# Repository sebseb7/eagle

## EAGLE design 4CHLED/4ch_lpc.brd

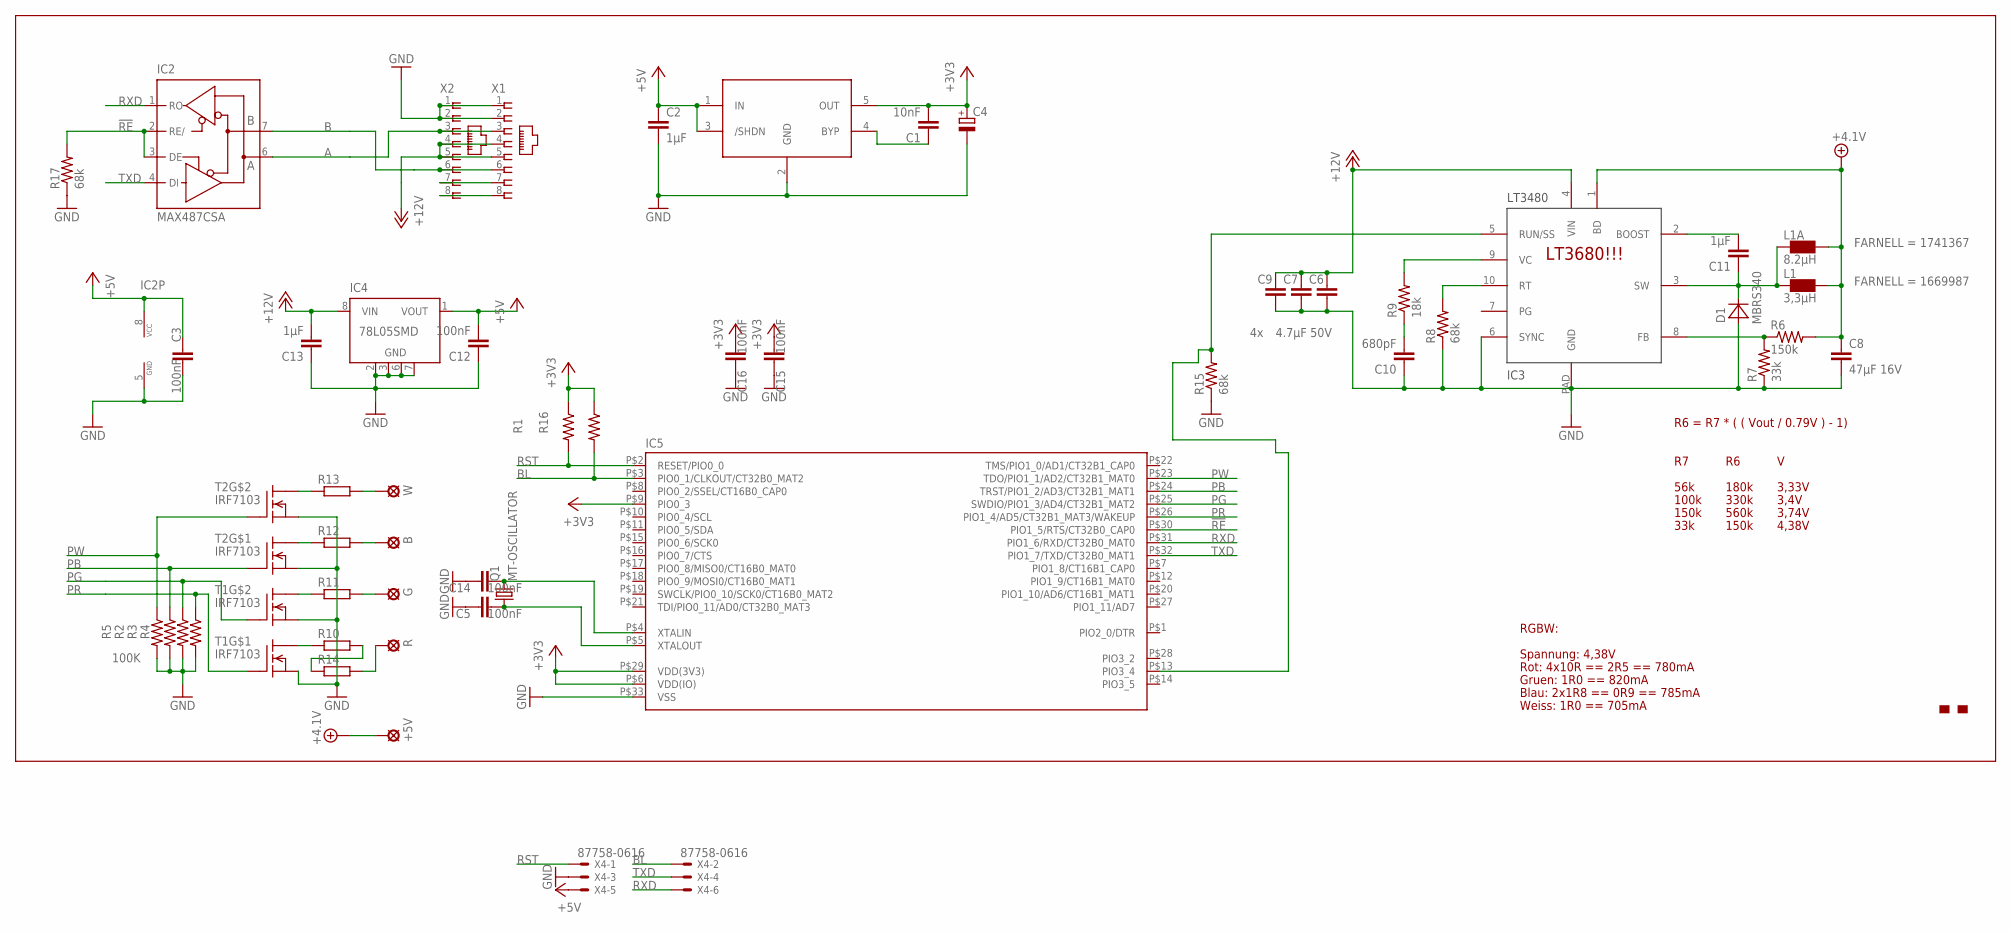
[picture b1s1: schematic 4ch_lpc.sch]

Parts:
+5V: SE14
B: SE14
C1: 10nF; C0402
C2, C11, C13: 1µF; 0805
C3, C5, C12, C14, C15, C16: 100nF; 0402-CAP
C4: CPOL-EUSMCA; SMC_A
C6, C7, C9: 4.7µF 50V; 1210
C8: 47µF 16V; 1210
C10: 680pF; 0805
D1: MBRS340; DO214AB
G: SE14
IC1: LT1761; SOT23-5L
IC2: MAX487CSA; SO08
IC3: LT3972; MSOP10-PAD
IC4: 78L05SMD; SO08
IC5: LPC1113/4_QFN; HVQFN33-7X7
L1: 3,3µH; RLF7030; FARNELL 1669987
L1A: 8.2µH; IHLP-2525CZ; FARNELL 1741367
Q1: MT-OSCILLATOR; MT
R: SE14
R1, R2, R3, R4, R5, R16: 100K; 0402-RES
R6: 150k; 0805
R7: 33k; 0805
R8: 68k; 0805
R9: 18k; 0805
R10, R11, R12, R13, R14: R-EU_MELF0207R; MINI_MELF-0207R
R15, R17: 68k; 0402-RES
T1, T2: IRF7103; SO-8
U$1: MAKE-DD_LOGO'PROMPT'; MAKE-DD_LOGO_PROMPT
W: SE14
X1, X2: RJ45-8L-B; RJ45-NO-SHIELD
X4: 87758-0616

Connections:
!RE: IC2.2 (RE/), IC2.3 (DE), IC5.P$30 (PIO1_5/RTS/CT32B0_CAP0), R17.2
+3V3: C1.2, C4.+, C15.2, C16.2, IC1.5 (OUT), IC5.P$6 (VDD(IO)), IC5.P$9 (PIO0_3), IC5.P$29 (VDD(3V3)), R1.1, R16.1
+4.1V: +5V.MP, C8.1, IC3.1 (BD), L1.P$1 (1), L1A.P$1 (1), R6.2
+5V: C2.1, C3.1, C12.2, IC1.1 (IN), IC1.3 (/SHDN), IC2.8 (VCC), IC4.1 (VOUT), X4.5
+12V: C6.1, C7.1, C9.1, C13.2, IC3.4 (VIN), IC4.8 (VIN), X1.4, X1.5, X2.4, X2.5
A: IC2.6 (A), X1.3, X2.3
B: IC2.7 (B), X1.6, X2.6
BL: IC5.P$3 (PIO0_1/CLKOUT/CT32B0_MAT2), R16.2, X4.2
GND: C2.2, C3.2, C4.-, C5.1, C6.2, C7.2, C8.2, C9.2, C10.1, C12.1, C13.1, C14.1, C15.1, C16.1, D1.A, IC1.2 (GND), IC2.5 (GND), IC3.6 (SYNC), IC3.PAD (GND), IC4.2 (GND), IC4.3 (GND), IC4.6 (GND), IC4.7 (GND), IC5.P$33 (VSS), R2.2, R3.2, R4.2, R5.2, R7.1, R8.1, R15.1, R17.1, T1.1 (S), T1.3 (S), T2.1 (S), T2.3 (S), X1.1, X1.2, X2.1, X2.2, X4.3
unnamed: R10.1, T1.8 (D1)
unnamed: R13.2, W.MP
unnamed: R13.1, T2.5 (D1)
unnamed: R11.1, T1.5 (D1)
unnamed: R12.1, T2.8 (D1)
unnamed: IC3.10 (RT), R8.2
unnamed: C1.1, IC1.4 (BYP)
unnamed: G.MP, R11.2
unnamed: B.MP, R12.2
unnamed: C10.2, R9.1
unnamed: R10.2, R14.1
unnamed: IC3.5 (RUN/SS), IC5.P$13 (PIO3_4), R15.2
unnamed: R.MP, R14.2
unnamed: IC3.9 (VC), R9.2
unnamed: C11.1, D1.K (C), IC3.3 (SW), L1.P$2 (2), L1A.P$2 (2)
unnamed: IC3.8 (FB), R6.1, R7.2
unnamed: C11.2, IC3.2 (BOOST)
unnamed: X1.7, X2.7
unnamed: X1.8, X2.8
unnamed: C5.2, IC5.P$5 (XTALOUT), Q1.1
unnamed: C14.2, IC5.P$4 (XTALIN), Q1.3 (2)
PB: IC5.P$24 (TRST/PIO1_2/AD3/CT32B1_MAT1), R2.1, T2.2 (G)
PG: IC5.P$25 (SWDIO/PIO1_3/AD4/CT32B1_MAT2), R3.1, T1.4 (G)
PR: IC5.P$26 (PIO1_4/AD5/CT32B1_MAT3/WAKEUP), R4.1, T1.2 (G)
PW: IC5.P$23 (TDO/PIO1_1/AD2/CT32B1_MAT0), R5.1, T2.4 (G)
RST: IC5.P$2 (RESET/PIO0_0), R1.2, X4.1
RXD: IC2.1 (RO), IC5.P$31 (PIO1_6/RXD/CT32B0_MAT0), X4.6
TXD: IC2.4 (DI), IC5.P$32 (PIO1_7/TXD/CT32B0_MAT1), X4.4

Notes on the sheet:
R6 = R7 * ( ( Vout / 0.79V ) - 1)
56k
180k
3,33V
100k
330k
3,4V
150k
560k
3,74V
33k
4,38V
RGBW:
Spannung: 4,38V
Rot: 4x10R == 2R5 == 780mA
Gruen: 1R0 == 820mA
Blau: 2x1R8 == 0R9 == 785mA
Weiss: 1R0 == 705mA
LT3680!!!

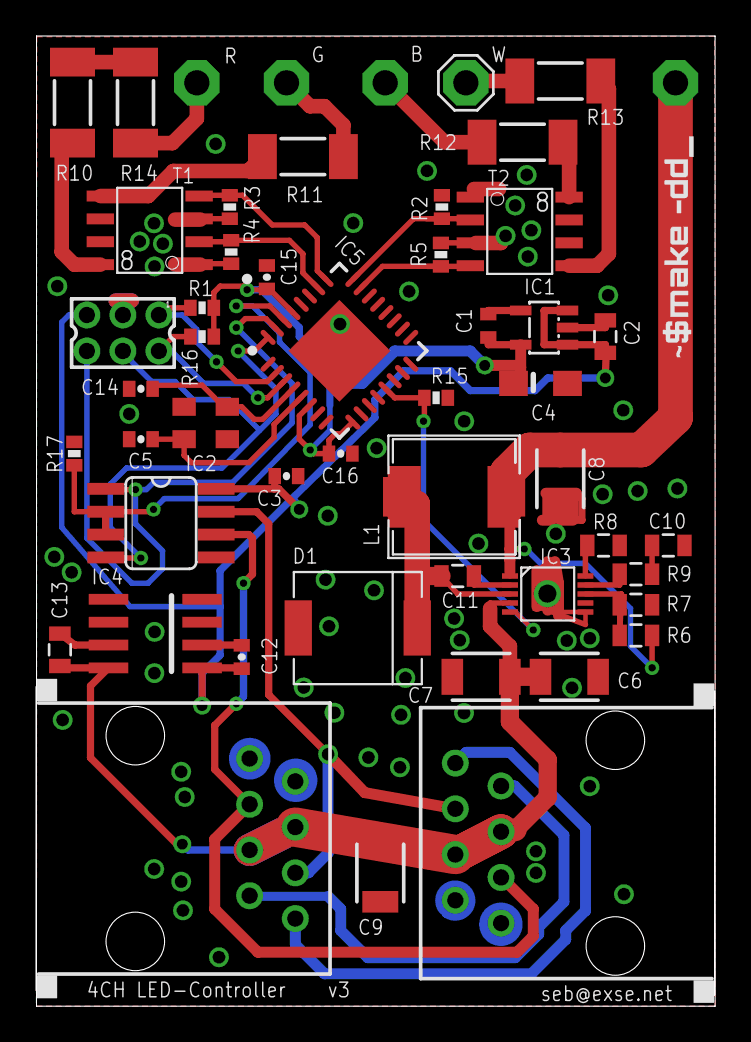
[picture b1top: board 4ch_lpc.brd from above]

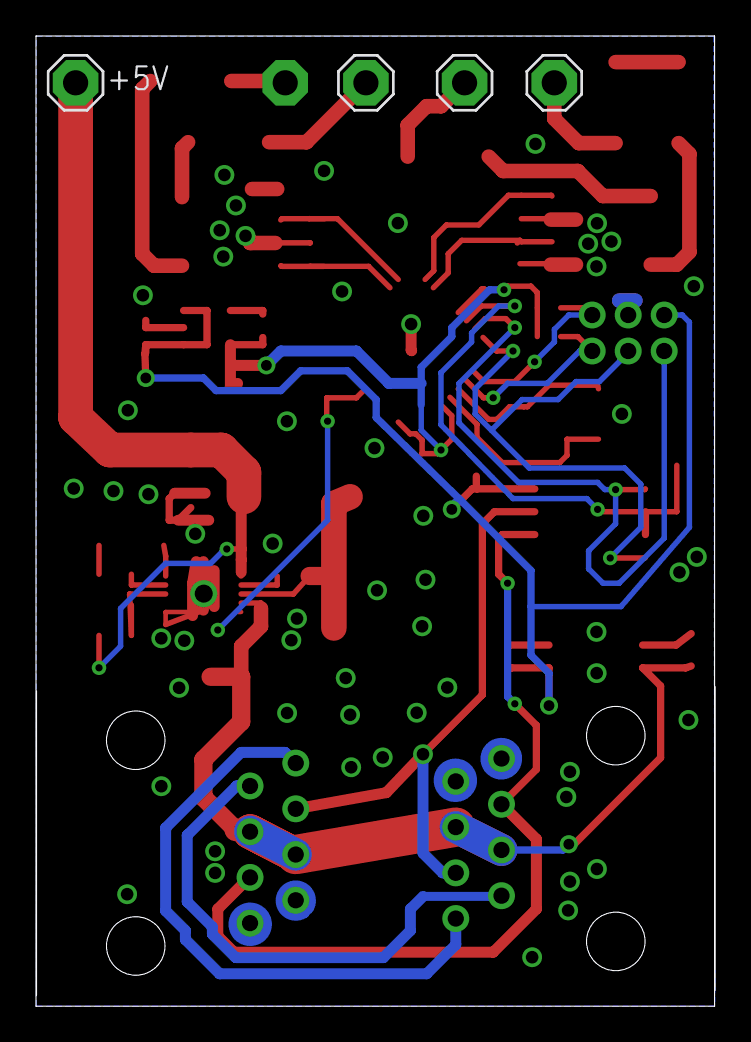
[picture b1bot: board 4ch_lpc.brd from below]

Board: 2 copper layers, 37.7 x 53.9 mm, 53 parts (4 on the bottom side), 37 nets.

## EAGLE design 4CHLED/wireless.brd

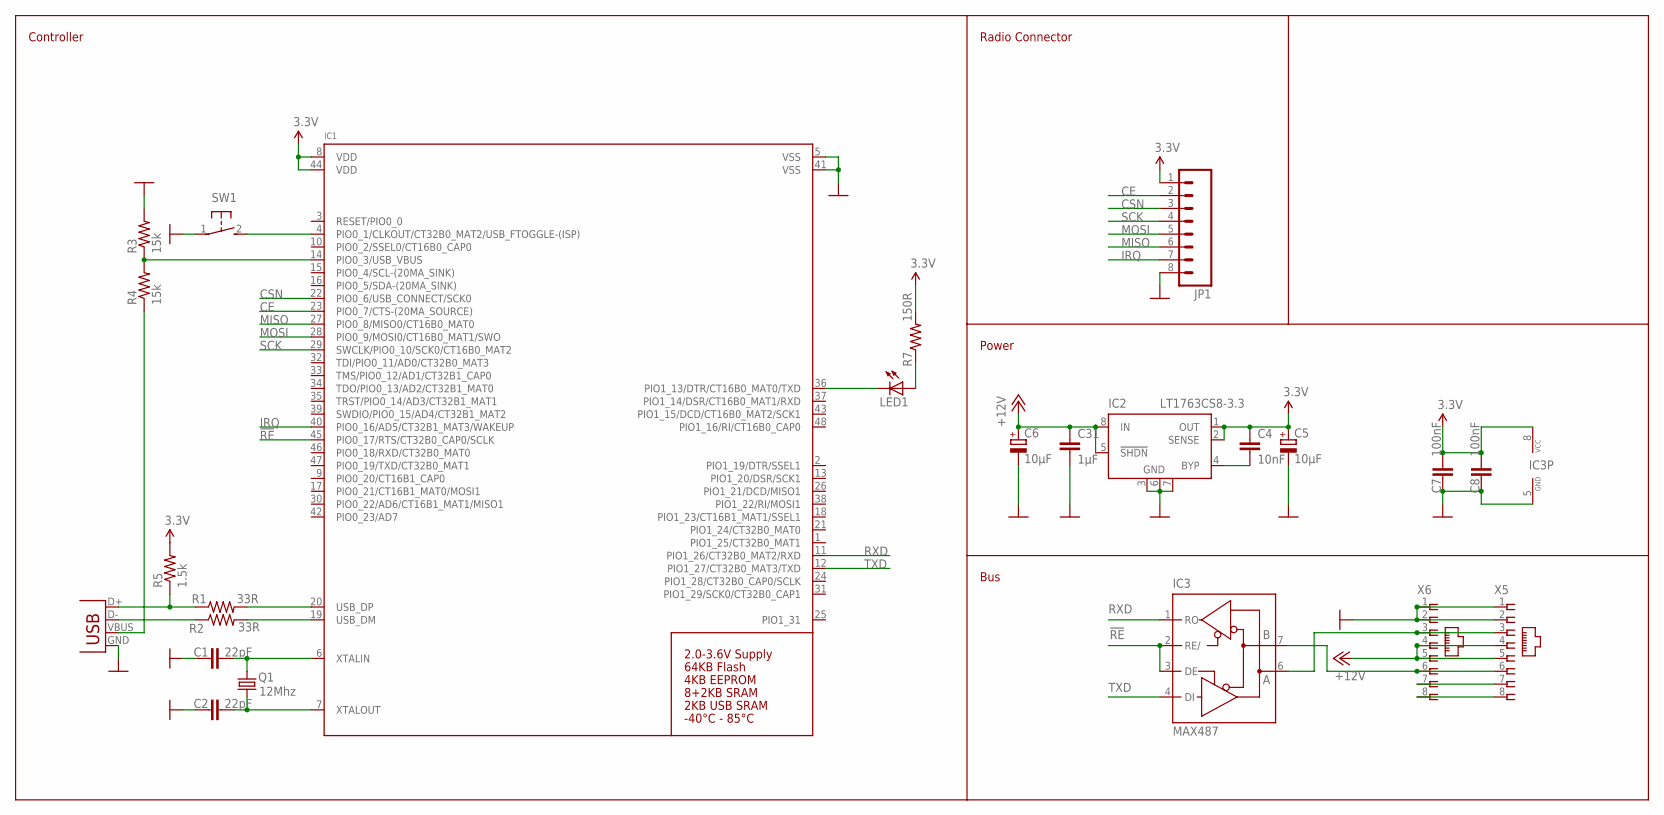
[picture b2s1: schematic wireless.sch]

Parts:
C1, C2: 22pF; 0402-CAP
C4: 10nF; 0402-CAP
C5: 10µF; SMC_A
C6: 10µF; SMC_D
C7, C8: 100nF; 0402-CAP
C31: 1µF; 0805
IC1: LPC1347_QFP48; LQFP48
IC2: LT1763CS8-3.3; SOIC8
IC3: MAX487; SO08
JP1: M081X08; 1X08
LED1: LEDCHIPLED_0805; CHIPLED_0805
Q1: 12Mhz; X22
R1, R2: 33R; 0402-RES
R3, R4: 15k; 0402-RES
R5: 1.5k; 0402-RES
R7: 150R; 0402-RES
SW1: SWITCH_MCTAEF
X1: USBSMD; USB-MINIB
X5, X6: RJ45-8L-B; RJ45-NO-SHIELD

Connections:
3.3V: C4.1, C5.+, C7.2, C8.2, IC1.8 (VDD), IC1.44 (VDD), IC2.1 (OUT), IC2.2 (SENSE), IC3.8 (VCC), JP1.1, R5.2, R7.2
!RE: IC1.45 (PIO0_17/RTS/CT32B0_CAP0/SCLK), IC3.2 (RE/), IC3.3 (DE)
+12V: C6.+, C31.1, IC2.5 (!SHDN), IC2.8 (IN), X5.4, X5.5, X6.4, X6.5
A1: IC3.6 (A), X5.3, X6.3
B1: IC3.7 (B), X5.6, X6.6
CE: IC1.23 (PIO0_7/CTS-(20MA_SOURCE)), JP1.2
CSN: IC1.22 (PIO0_6/USB_CONNECT/SCK0), JP1.3
GND: C1.1, C2.1, C5.-, C6.-, C7.1, C8.1, C31.2, IC1.5 (VSS), IC1.41 (VSS), IC2.3 (GND), IC2.6 (GND), IC2.7 (GND), IC3.5 (GND), JP1.8, R3.2, SW1.1, X1.GND, X5.1, X5.2, X6.1, X6.2
IRQ: IC1.40 (PIO0_16/AD5/CT32B1_MAT3/WAKEUP), JP1.7
MISO: IC1.27 (PIO0_8/MISO0/CT16B0_MAT0), JP1.6
MOSI: IC1.28 (PIO0_9/MOSI0/CT16B0_MAT1/SWO), JP1.5
unnamed: C2.2, IC1.7 (XTALOUT), Q1.1
unnamed: C1.2, IC1.6 (XTALIN), Q1.3 (2)
unnamed: IC1.20 (USB_DP), R1.2
unnamed: IC1.19 (USB_DM), R2.2
unnamed: R1.1, R5.1, X1.D+
unnamed: R2.1, X1.D-
unnamed: R4.1, X1.VBUS
unnamed: IC1.14 (PIO0_3/USB_VBUS), R3.1, R4.2
unnamed: IC1.4 (PIO0_1/CLKOUT/CT32B0_MAT2/USB_FTOGGLE-(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), SW1.2
unnamed: IC1.36 (PIO1_13/DTR/CT16B0_MAT0/TXD), LED1.C
unnamed: C4.2, IC2.4 (BYP)
unnamed: LED1.A, R7.1
RXD: IC1.11 (PIO1_26/CT32B0_MAT2/RXD), IC3.1 (RO)
SCK: IC1.29 (SWCLK/PIO0_10/SCK0/CT16B0_MAT2), JP1.4
SPARE1: X5.7, X6.7
SPARE2: X5.8, X6.8
TXD: IC1.12 (PIO1_27/CT32B0_MAT3/TXD), IC3.4 (DI)

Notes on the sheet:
Radio Connector
Power
Bus
Controller

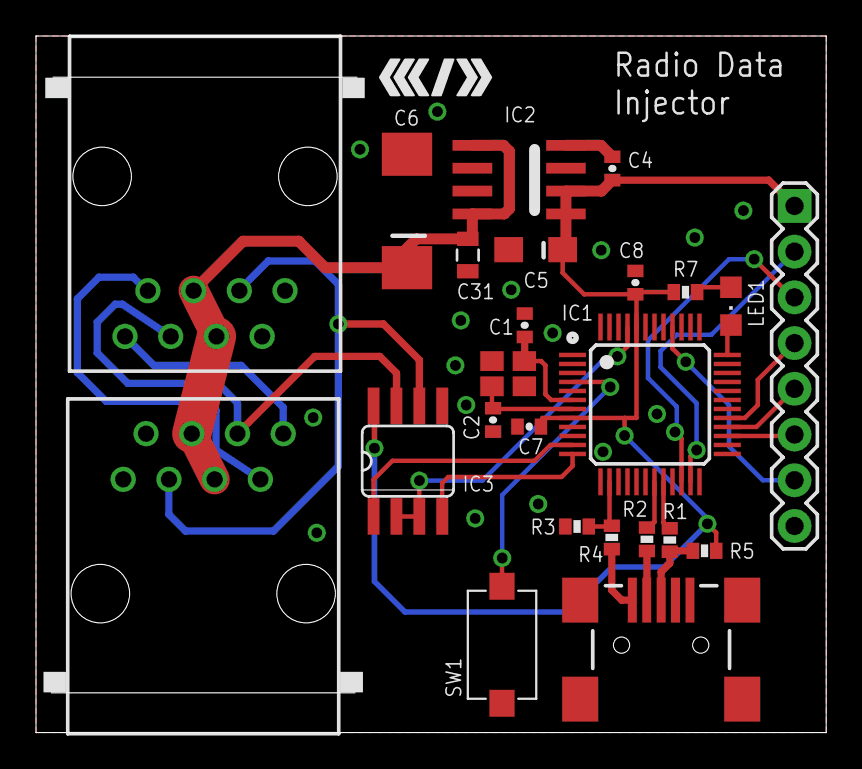
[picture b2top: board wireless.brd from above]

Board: 2 copper layers, 43.9 x 38.7 mm, 25 parts (0 on the bottom side), 28 nets.

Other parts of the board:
U$2: C3D2_LOGO_SMALL

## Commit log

2011-06-27 init
2011-06-28 minor tweaks
2011-06-29 initial version
2011-06-29 initial
2011-06-29 rename
2011-06-29 path fix
2011-06-29 path fix again
2011-06-29 added connector for nRF24LU1
2011-06-29 new version with m644pa and improoved routing
2011-06-29 decoupled AVCC/AREF
2011-06-30 added version v3 with included nRF24L01
2011-06-30 minor routing optimizations
2011-06-30 added .gitignore
2011-06-30 new images
2011-06-30 small layout fixes
2011-06-30 added .sch image
2011-07-04 added through hole version
2011-07-04 added spektrum to ppm converter
2011-07-04 added pcb image
2011-07-04 schematics beautify
2011-07-04 typo
2011-07-06 ignore
2011-07-06 small changes
2011-07-07 first version (not yet working)
2011-07-07 readme
2011-07-09 renamed
2011-07-09 small clean-ups
2011-07-11 ftdi uart bridge
2011-07-11 rearrange repo
2011-07-11 made link relative
2011-07-13 minor doc update
2011-07-13 initial version, non functional
2011-07-15 layout changes
2011-07-17 decoupled 2nd input pin for START
2011-07-19 GND layer fixes
2011-07-19 complete makeover, is now a lite version of v3
2011-07-19 enlaged button stop-area
2011-07-19 SparkFun lbr
2011-07-19 various parts lbr
2011-07-19 tlc led driver
2011-07-19 corrected 12V connection
2011-07-19 switching regulator 1.5A 3.3V or 5V
2011-07-20 preparations for production
2011-07-31 BAT was not connected to an ADC
2011-07-31 added FTDI
2011-07-31 rerouting: freed JTAG, freed i2c, freed 2nd UART, all cursor buttons on same port now
2011-07-31 changed start-button transistor
2011-08-04 fixed ic-to-ic connections
2011-08-04 added 0805 diode
2011-08-04 added mos capacitor values
2011-08-04 added missing values
2011-08-04 improvements for high-power (>100mA) bus-powered mode
2011-08-04 added silkscreen layer
2011-08-04 beautified schematics
2011-08-04 added new images of v2
2011-08-04 m644 -> m644pa
2011-08-07 file rename
2011-08-07 readded 2.0 version
2011-08-07 added fixing instuctions and values
2011-08-07 added tValues layer
2011-08-07 added 0805 inductor & bead
2011-08-07 changed inductor packages & added two more capacitors
2011-08-09 wrong RX / TX naming
2011-08-09 enlarged guide-holes
2011-08-09 added decicated battery PADs
2011-08-09 removeda GND Pad
2011-08-16 misc changes
2011-08-16 added battery pad
2011-08-17 fixed direction of diode
2011-08-17 exchanged power_off and irq
2011-08-17 initial firmware code
2011-08-17 ingnore compiled files
2011-08-17 exchanged usbsense and irq
2011-08-17 differend usbsense logic & led placement improoved
2011-08-17 usbsense pullup
2011-08-17 small debounce fixes
2011-08-17 new button layout
2011-08-17 board rezise and new buttons
2011-08-17 small updates
2011-08-17 new inductor
2011-08-18 added new project
2011-08-19 Version bump (v2.1 is in production)
2011-08-19 moved buttons and isp
2011-08-19 fixed some pins
2011-08-19 added two missing headers
2011-08-19 QFN Layout changed
2011-08-19 corrected version number
2011-08-20 fixes to get the new module work
2011-08-20 exchanged key a and b
2011-08-24 added GPOIR2 as bootloader invocation switch
2011-08-24 added mega88
2011-08-27 added TRACO TDR 2-xxxx
2011-08-27 added Traco TDR 2
2011-08-29 relocated ADDR lines, added ISP
2011-08-29 added FTDI and Strapuxbox 2029 case
2011-08-29 made connectors more robust (solid connection to GND)
2011-08-29 minor tweaks to the gnd layer and capacitor placement
2011-08-29 no stop on Commodore Logo
2011-08-30 fixed path
2011-08-30 final design for production
2011-08-31 added demo song, recorded on the SIDInterface module
2011-08-31 initial firmware
2011-08-31 added m644pa defs, plattform specific wdt reset, correct response to 0x1B
2011-08-31 moved to another repo
2011-09-02 initial checkin
2011-09-02 added AAA battery holder
2011-09-03 added RTS/CTS
2011-09-04 new project
2011-09-04 better layout
2011-09-04 initial firmware & bootloader
2011-09-06 optimizations
2011-09-06 added battery holder and uart pins
2011-09-08 poweroff and poweron changes
2011-09-08 move pentalight to other repo
2011-09-09 cleanup
2011-09-09 removed eagle.epf files
2011-09-09 added inductor
2011-09-10 another inductor
2011-09-14 new parts
2011-09-14 added Nichia SMD LED and fixed Prefix for all parts
2011-09-14 added a Nichia High Power White LED
2011-09-14 added gitignore
2011-09-14 added type 1 compensator
2011-09-14 tPlace changes
2011-09-23 firmware initial checkin
2011-09-24 initial firmware checkin
2011-09-29 added mpu-6050
2011-09-29 tuning
2011-10-05 new projects: ledstick2 and mpu6050 breakout
2011-10-08 minor changes
2011-10-25 ctrl board
2011-10-25 small fixes
2011-10-26 added smt receptables
2011-10-26 beta version done
2011-10-27 final tweaks
2011-10-31 added PISR and DO214AB
2011-10-31 smaller Capacitors, couple of corrections
2011-10-31 small corrections
2011-11-04 some changes
2011-11-04 resize
2011-11-04 polygon optimization
2011-11-04 fixed powerdi 123
2011-11-04 moved
2011-11-05 added dru file for pcbcart
2011-11-06 added tdk inductor
2011-11-06 changed regulator
2011-11-07 added power injector
2011-11-07 added alternative inductor
2011-11-07 added simple data injector
2011-11-15 added 4 pin smd headers
2011-11-20 added firmware for version2 POI
2011-11-20 fixes and enhancements
2011-11-20 changed battery app
2011-11-20 minimized header inclusions
2011-11-20 optimized part placement
2011-11-20 merge
2011-11-21 gitignore update
2011-11-21 added lpc111x testboard
2011-11-30 added LT1933
2011-12-07 testboard
2011-12-08 values
2011-12-16 hsl_to_rgb fader
2011-12-20 0402
2012-01-03 wdt reset
2012-01-03 replaced mcu symbol
2012-01-04 new button 0603->0402
2012-01-04 new buttons
2012-01-04 begun remodelling
2012-01-09 mosfet
2012-01-09 opto
2012-01-10 display
2012-01-14 serial communication working
2012-01-17 added LM3401
2012-01-17 new testboard for lm3401
2012-01-21 microbuilder.lbr
2012-01-27 examples
2012-01-27 updates & pentawallHD compatibility
2012-01-27 pentawallHD compatible
2012-02-02 not yet done
2012-02-02 sync
2012-02-02 some routing for signal injector done
2012-02-02 last airwires
2012-02-02 improved groundplanes
2012-02-03 print optimized
2012-02-03 reduced some thermals at VCC for better conductivity, some minor improvements in component placemen print
2012-02-04 Capacitor Board added
2012-02-05 fixed glitch in schematics for data injector wich connected TXD_AL, TDXEN and Pin 3 of OK1 and OK 1
2012-02-05 fixed wrong routing caused by the schematics glitch that connected TXD_AL and TDXEN etc.
2012-02-05 R20, R21, R23 were no longer required
2012-02-05 Data Injector: C17 and C18 removed, Replaced Resitors with 0805
2012-02-05 C14,C19,C21 and L2 closer togehther, additional C for MAX 487
2012-02-05 some unroutetd and power supply for max487 fixed
2012-02-05 component values for data injector board checked
2012-02-05 tplace placement print and values placed
2012-02-05 improved placement of several components for data injector
2012-02-05 fixed mirrored rj45 on capacitor board
2012-02-05 placement print for capacitor board
2012-02-05 added schottky protection diode to power injector, all wires of power inmjector connected (signal ones especially, solder pads for PI and flex relief (strain relief) drills forpower supply cables add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
2012-02-05 fixed some unrouted airwires in 4ch led controller
2012-02-05 mved strain relieve drills of power injector half a millimeter away from board edges
2012-02-05 placement print for power inhjector
2012-02-06 panel
2012-02-06 cosmetics
2012-02-08 new variant using lm3401
2012-02-08 placement print improved, clearance on one spiky polygon edge with +18V improved
2012-02-11 removed
2012-02-11 hsv strobe
2012-02-11 new demo files
2012-02-11 beta
2012-02-21 random changes
2012-02-26 number of smaller fixes
2012-02-26 routing done
2012-02-26 copy silkscreen for panelizing
2012-02-26 updated 4chled v2, added 4chled v3 & Highpower-Pentafnord-Module
2012-02-28 firmware
2012-02-28 fixes and spec_pwr
2012-02-28 spec board
2012-02-28 misc
2012-02-28 even more cleanup
2012-02-28 removed gnd wire
2012-03-01 create gerber from cmdline
2012-03-01 fixes
2012-03-01 removed tmp
2012-03-10 nice
2012-03-11 tab routing
2012-03-11 batBeep
2012-03-11 lt1933
2012-03-20 t8 mini sw
2012-04-11 new crystal
2012-06-02 made id smaller
2012-06-02 removed build files
2012-06-05 some change
2012-07-29 Added Farnell Battery Holder # 1650679
2012-07-29 changed prefix to BAT
2012-07-30 minor changes to the 2xAAA holder
2012-09-12 use the office git repo
2012-09-12 eagle 6 version
2012-10-15 added logo
2012-10-20 abm3
2012-10-23 radio data injector
2012-10-25 readded
2012-10-25 new devices
2013-02-21 new connectors and new logo
2013-02-21 logo variant
2013-02-21 prompt fix
2013-03-19 added LPC81X
2013-03-20 added tssop20 tssop28 hvqfn24 hvqfn32
2013-03-20 jst connectors
2013-03-20 ml-621 battery
2013-04-06 added HR961160C smt rj45 connector with magnetics and leds
2013-06-27 lpc variant
2013-06-27 minor change to hqfn33
2013-06-27 final touches for production
2013-06-27 rs485 shielding
2013-06-27 show top layer
2013-06-27 move via
2013-06-27 added ea dogmxxx-a display
2013-07-05 added traco power converter
2013-07-05 lm3402 incomplete
2013-07-08 completed lm3402

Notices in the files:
parts and their libraries:
microbuilder: This work is placed in the public domain, and may be freely used for commercial and non-commercial work with the following conditions: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
SparkFun-Capacitors: Licensing: CC v3.0 Share-Alike You are welcome to use this library for commercial purposes.
